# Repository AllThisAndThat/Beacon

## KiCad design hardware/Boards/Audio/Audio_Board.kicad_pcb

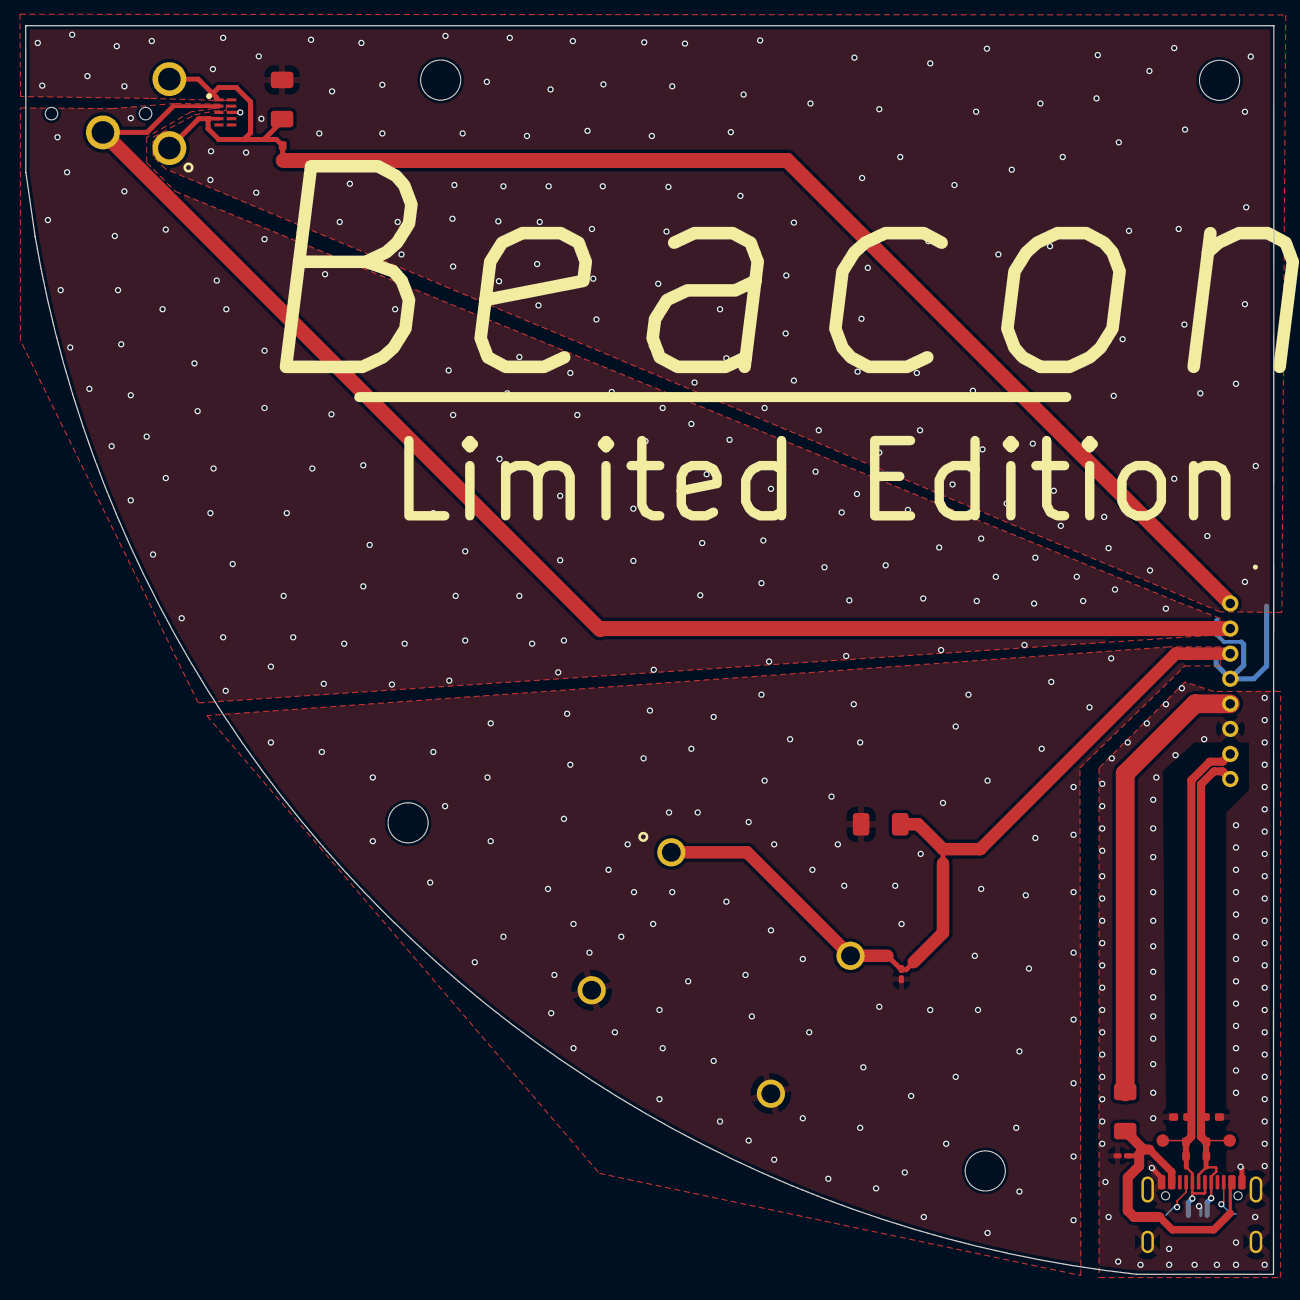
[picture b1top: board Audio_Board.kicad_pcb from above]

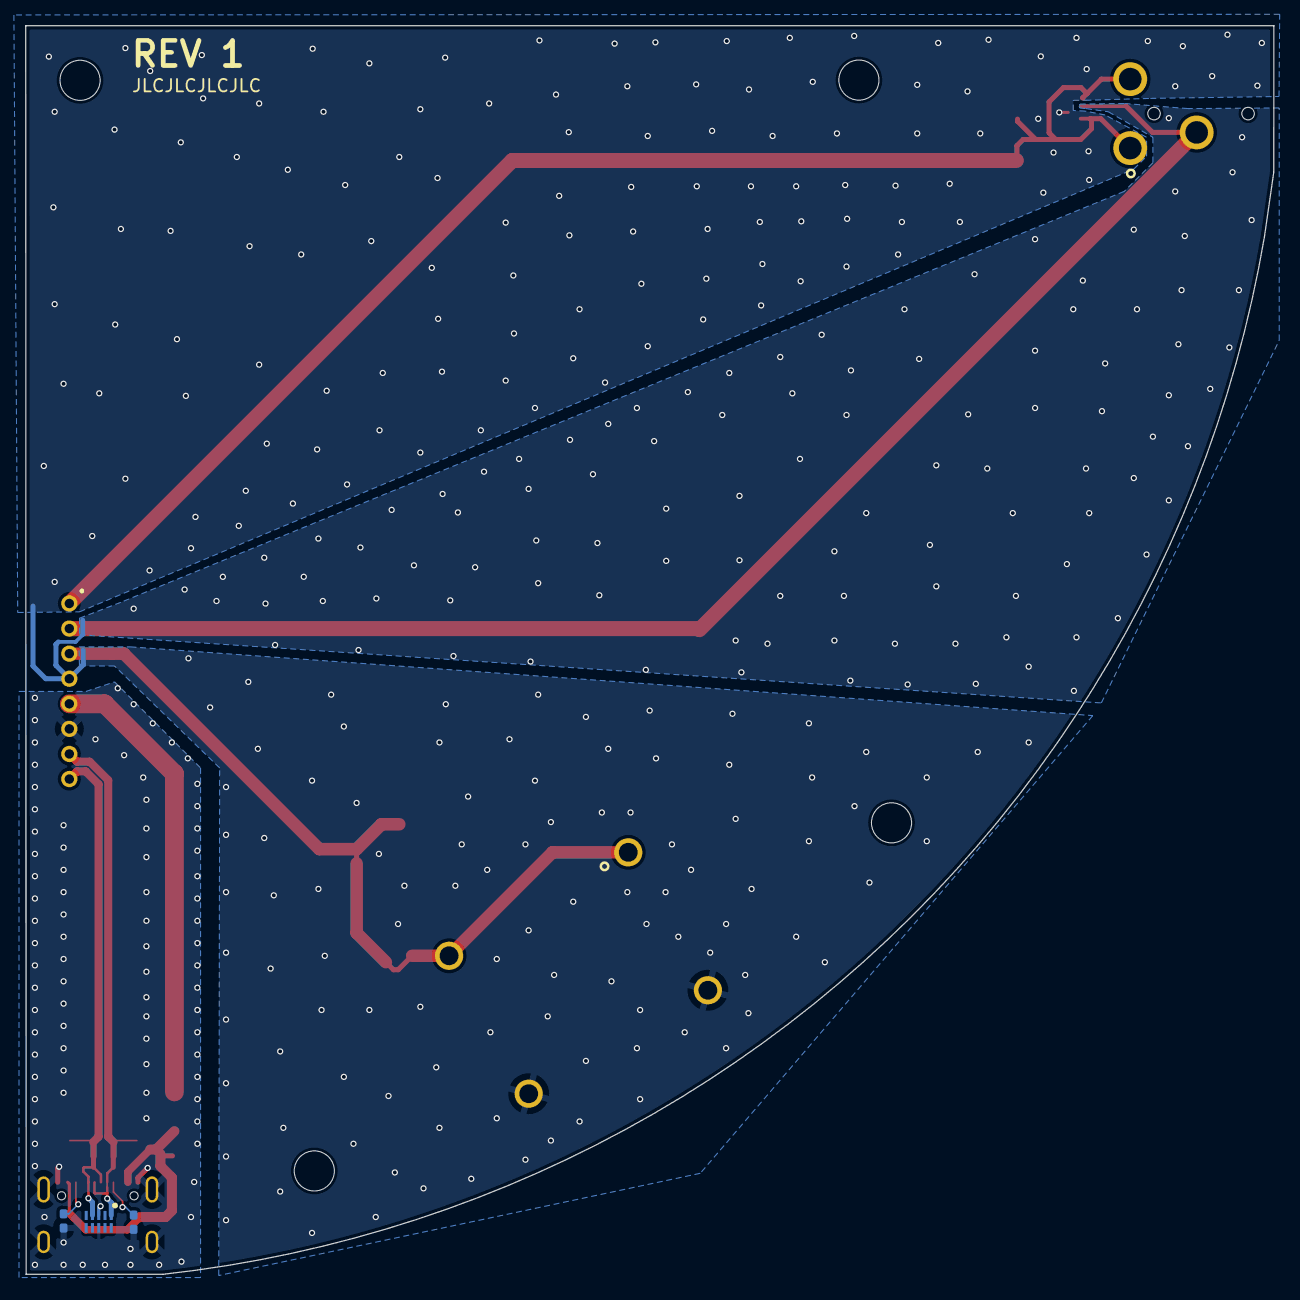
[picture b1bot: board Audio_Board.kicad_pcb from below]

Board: 6 copper layers, 99.5 x 99.6 mm, 22 parts (3 on the bottom side), 10 nets.

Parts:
Audio: Board
C509, C514: 1u00_1206_10_T; 1206_3216Metric_Handsolder
C531, C532: ????_0402_25; 0402_1005Metric_Handsolder
D502: ESDZV5HS-1BF4; 0201_0804Metric_Handsolder
D504, D505: PESD4USB5B; PESD4USB5BTBSX
D506: TVSL02V03C011; 0201_0804Metric_Handsolder
F502: 1A1_1206_08; 1206_3216Metric_Handsolder
J105: Conn_01x08_Pin; CONN_1x08_P2.00mm_Horizontal
J503, J505, J508, J511: 0402; 0402_CUT-N-JUMP
J509: Conn_01x03_Pin; STX3000
J510: USB_C_Receptacle_USB2.0; USB4105-GF-A
J513: Conn_01x02_Pin; NYS2162U
R517, R518: 5k10_0402_010; 0402_1005Metric_Handsolder
TP507: USB_DN; Testpoint_Pad_D1.0mm
TP508: USB_DP; Testpoint_Pad_D1.0mm

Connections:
Board_0-/Audio_Board/+5V: F502.2, J105.5
Board_0-/Audio_Board/AUDIO_GND_SEN: D504.2, J105.2, J509.2
Board_0-/Audio_Board/AUDIO_HP: C509.1, D504.1, D504.4, J105.1, J503.1, J503.2, J509.1, J509.3
Board_0-/Audio_Board/AUDIO_SP: C514.1, D506.1, J105.3, J505.1, J505.2, J513.1
Board_0-/Audio_Board/USB_DN: C531.2, D505.1, J105.7, J508.1, J508.2, J510.A7 (D-), J510.B7 (D-), TP507.1
Board_0-/Audio_Board/USB_DP: C532.2, D505.4, J105.8, J510.A6 (D+), J510.B6 (D+), J511.1, J511.2, TP508.1
Board_0-GND: C509.2, C514.2, C531.1, C532.1, D502.2, D504.3 (GND), D504.8 (GND), D505.3 (GND), D505.8 (GND), D506.2, J105.4, J105.6, J510.A1 (GND), J510.A12 (GND), J510.B1 (GND), J510.B12 (GND), J510.S1 (SHIELD), J513.2, R517.1, R518.1
Board_0-Net-(D502-Pad1): D502.1, F502.1, J510.A4 (VBUS), J510.A9 (VBUS), J510.B4 (VBUS), J510.B9 (VBUS)
Board_0-Net-(J510-CC1): J510.A5 (CC1), R517.2
Board_0-Net-(J510-CC2): J510.B5 (CC2), R518.2

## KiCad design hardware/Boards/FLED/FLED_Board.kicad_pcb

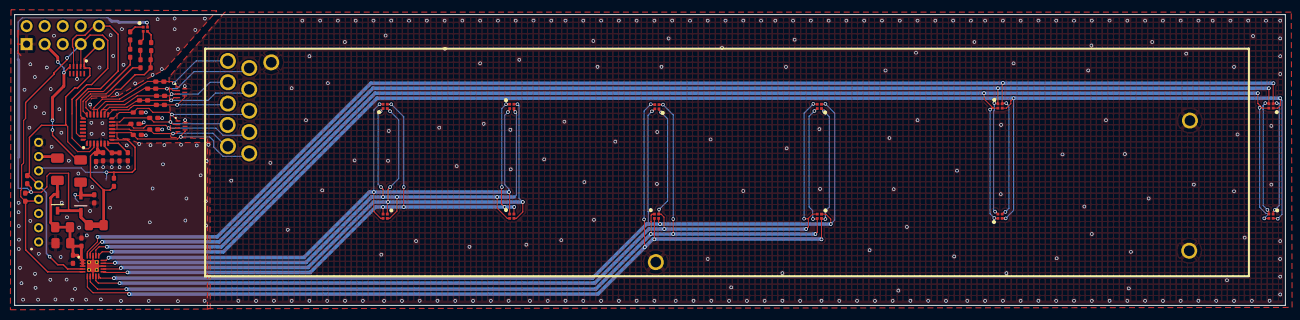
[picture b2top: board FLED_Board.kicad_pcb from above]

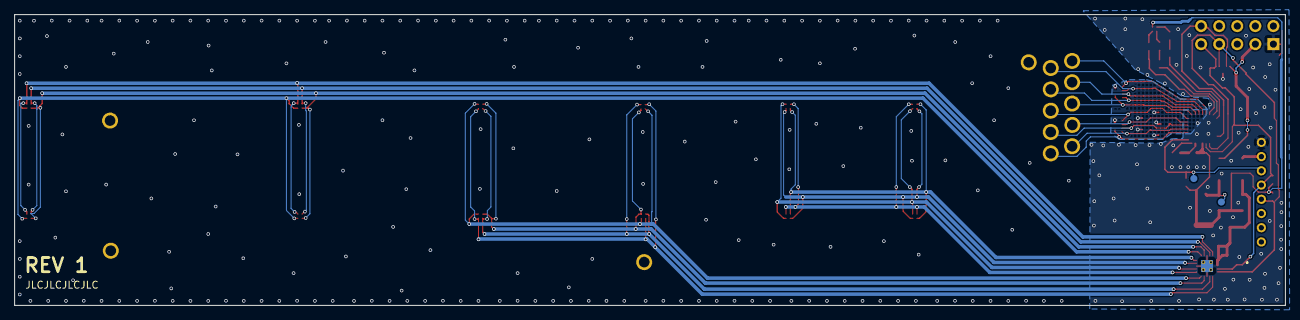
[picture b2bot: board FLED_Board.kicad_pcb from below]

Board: 6 copper layers, 178.7 x 40.9 mm, 71 parts (3 on the bottom side), 42 nets.

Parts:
C303, C403, C404, C408: 1u00_0402_10; 0402_1005Metric_Handsolder
C401, C407, C409: 100n_0402_16; 0402_1005Metric_Handsolder
C402: 10u0_0805_16; 0805_2012Metric_Handsolder
C405: 10n0_0402_25; 0402_1005Metric_Handsolder
C406, C410, C411, C412, C413: ????_0402_25; 0402_1005Metric_Handsolder
D401, D402, D403, D404, D405, D406, D407, D408, D409, D410, D411, D412, D417: UHD1110; UHD1110FKACL1A13r3q1BBQFMF3
D413, D414: 1N4148WX-TP; SOD2512X115N
D415: PESD4USB5B; PESD4USB5BTBSX
D416, D418: PUSB3TB6AZ
F401, F402: 1A1_1206_08; 1206_3216Metric_Handsolder
FLED: Board
H401, H402, H403, H404, H405, H411, H413, H415, H417, H423, H425, H426, H427, H428: Plated_Through_Hole; Plated_Hole_D1.5mm
J102: Conn_01x08_Pin; CONN_1x08_P2.00mm_Horizontal
J401, J408: 0805; 0805_CUT-N-JUMP
J402, J403, J405, J406, J407, J409: 0402; 0402_CUT-N-JUMP
J404: Conn_02x05_Odd_Even; PinHeader_2x05_P2.54
R401, R402: 4k70_0402_010; 0402_1005Metric_Handsolder
R403: 1k00_0402_010; 0402_1005Metric_Handsolder
R405, R407: 0330_0402_010; 0402_1005Metric_Handsolder
R406, R408: 0100_0402_010; 0402_1005Metric_Handsolder
R409: 47k0_0402_010; 0402_1005Metric_Handsolder
TP401: TOUCH_INT; Testpoint_Pad_D1.0mm
TP403: +3V3_DEBUG; Testpoint_Pad_D1.0mm
U401: KTD20XXEUAC-TR; UQFN-20-1EP_3x3mm_P0.4mm_EP1.7x1.7mm_ThermalVias
U402: IQS525BLQNR; QFN-28_4x4mm_P0.5mm

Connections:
Board_0-/Fret_Assembly/+3V3: C303.2, C401.2, C402.2, D413.2 (A), F401.2, J401.1, J401.2, U401.1 (VIN), U401.2 (VIN), U401.3 (VCC)
Board_0-/Fret_Assembly/+3V3_DEBUG: D415.5, F402.1, J404.3
Board_0-/Fret_Assembly/+3V3_EXT: F401.1, J102.7
Board_0-/Fret_Assembly/+3V3_PROTECT: C403.2, C405.2, D413.1 (K), D414.1 (K), D417.4, J408.1, J408.2, R401.2, R402.2, R409.1, U402.4 (VDDHI)
Board_0-/Fret_Assembly/BLED: R408.1, U402.22 (PD4)
Board_0-/Fret_Assembly/GLED: R406.1, U402.21 (PD3)
Board_0-/Fret_Assembly/I2C1_SCLK: D415.1, J102.5, J404.9, R401.1, U401.4 (SCL), U402.3 (SCL)
Board_0-/Fret_Assembly/I2C1_SDA: D415.2, J102.4, J404.7, R402.1, U401.5 (SDA), U402.2 (SDA)
Board_0-/Fret_Assembly/LEDA1: D401.3, D402.2, D403.1, D404.4, U401.6 (LEDA1)
Board_0-/Fret_Assembly/LEDA2: D401.2, D402.1, D403.4, D404.3, U401.7 (LEDA2)
Board_0-/Fret_Assembly/LEDA3: D401.1, D402.4, D403.3, D404.2, U401.9 (LEDA3)
Board_0-/Fret_Assembly/LEDA4: D401.4, D402.3, D403.2, D404.1, U401.10 (LEDA4)
Board_0-/Fret_Assembly/LEDB1: D405.3, D406.2, D407.1, D408.4, U401.11 (LEDB1)
Board_0-/Fret_Assembly/LEDB2: D405.2, D406.1, D407.4, D408.3, U401.12 (LEDB2)
Board_0-/Fret_Assembly/LEDB3: D405.1, D406.4, D407.3, D408.2, U401.14 (LEDB3)
Board_0-/Fret_Assembly/LEDB4: D405.4, D406.3, D407.2, D408.1, U401.15 (LEDB4)
Board_0-/Fret_Assembly/LEDC1: D409.3, D410.2, D411.1, D412.4, U401.16 (LEDC1)
Board_0-/Fret_Assembly/LEDC2: D409.2, D410.1, D411.4, D412.3, U401.17 (LEDC2)
Board_0-/Fret_Assembly/LEDC3: D409.1, D410.4, D411.3, D412.2, U401.19 (LEDC3)
Board_0-/Fret_Assembly/LEDC4: D409.4, D410.3, D411.2, D412.1, U401.20 (LEDC4)
Board_0-/Fret_Assembly/RLED: J409.1, J409.2, R403.1, U402.20 (PD2)
Board_0-/Fret_Assembly/RX0: C406.2, D418.5, H411.1, U402.10 (RX0/TX9)
Board_0-/Fret_Assembly/RX1: C410.2, D418.4, H413.1, U402.11 (RX1/TX8)
Board_0-/Fret_Assembly/RX2: C411.2, D418.3, H415.1, U402.12 (RX2/TX7)
Board_0-/Fret_Assembly/RX3: C412.2, D418.2, H417.1, U402.13 (RX3/TX6)
Board_0-/Fret_Assembly/RX4: C413.2, D418.1, H423.1, U402.14 (RX4/TX5)
Board_0-/Fret_Assembly/TOUCH_INT: J102.6, R409.2, TP401.1, U402.8 (RDY)
Board_0-/Fret_Assembly/TOUCH_PROGM: D415.4, J404.10, U402.27 (PGM)
Board_0-/Fret_Assembly/TX0: D416.1, H401.1, J402.1, J402.2, U402.19 (TX0)
Board_0-/Fret_Assembly/TX1: D416.2, H402.1, J403.1, J403.2, U402.18 (TX1)
Board_0-/Fret_Assembly/TX2: D416.3, H403.1, J405.1, J405.2, U402.17 (RX7/TX2)
Board_0-/Fret_Assembly/TX3: D416.4, H404.1, J406.1, J406.2, U402.16 (RX6/TX3)
Board_0-/Fret_Assembly/TX4: D416.5, H405.1, J407.1, J407.2, U402.15 (RX5/TX4)
Board_0-GND: C303.1, C401.1, C402.1, C403.1, C404.1, C405.1, C406.1, C407.1, C408.1, C409.1, C410.1, C411.1, C412.1, C413.1, D415.3 (GND), D415.8 (GND), D416.7 (GND), D418.7 (GND), H425.1, H426.1, H427.1, H428.1, J102.8, J404.1, U401.8 (GND), U401.13 (GND), U401.18 (GND), U401.EP (GND), U402.5 (VSS)
Board_0-Net-(D414-A): C404.2, D414.2 (A), F402.2, TP403.1
Board_0-Net-(D417-Pad1): D417.1, R407.2
Board_0-Net-(D417-Pad2): D417.2, R405.2
Board_0-Net-(D417-Pad3): D417.3, R403.2
Board_0-Net-(R405-Pad1): R405.1, R406.2
Board_0-Net-(R407-Pad1): R407.1, R408.2
Board_0-Net-(U402-NRST): C409.2, U402.7 (NRST)
Board_0-Net-(U402-VREG): C407.2, C408.2, U402.6 (VREG)

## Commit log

2024-10-27 Working on new pinManager concept
2024-12-01 Got Uart_printing working
2024-12-02 Got LED controller driver wrapper library working
2024-12-12 Added functionality to LedDriver
    * Setup test for LedDriver
    * Set heartbeat in main to freertos task
    * Added the following:
    * On and off functions
    * Bad duty rejection
    * Duty to resolution adjustment.
2024-12-15 Got Status_LED libary functioning
    Made small fixes to Led_Driver.
    Renamed/reorganized pin_assignment to reserved_objects.
    Created and got status_led working.
    Started a timer.h wrapper.
2024-12-23 Worked on Spi and I2C classes
2024-12-28 Wrote LTR_303ALS driver
2024-12-28 KTS1622 Driver started
    * Wrote test for ambient light sensor
    * Started kts1622 driver
2024-12-29 Started I2S and Max9867 drivers
    * Made test for kts1622
    * Created driver for i2s
    * Created driver for max9867
    * Polished kts1622 - removed interrrupts on esp side and added debounce fuctionality
2025-01-05 Progress on max9867
    * Headphone output detect working
    * Started I2S communication between ICs
2025-01-16 Got CODEC Echo working
2025-01-20 Significant progress on Max9867
    * added DAC I2C commands
    * added ADC I2C commands
    * added task for audio processing
2025-01-27 Started work on IMU
    * Developed SPI and BMI323 drivers
    * Renamed and reordered reserve library
2025-02-02 Significant progress on BMI323
    * Read, write, and multiread registers working.
    * BMI323 configuration working
    * Reading acc and gyro data successfully
2025-02-06 Started IS31FL3741 driver
    * Class setup
    * Initiate
    * Unlock
    * Some configuration registers
2025-02-09 Implemented several IS31fl3741 methods
    * Reset all leds
    * Set specific led by num
    * set specific led by row, column, color
2025-02-13 Improvements to IS31FL3741 driver
    * Created set_rgb_led method with improved clarity
    * Fixed reset fails first time bug
    * Fixed ghosting bug
2025-03-03 Started CAP1188 driver
2025-04-14 Starting Beacon Lite Version
    * Achieved Old hardware files for reference.
    * Started new Kicad Design
2025-04-20 Started ST project. Create sch symbols.
2025-04-23 Minor schematic and symbol updates
2025-05-09 Started programming NUCLEO-H533 in VSCODE
    * Able to use C++ and C
    * Successful able to debug
    * Can blink an LED when button is pressed via an interrupt.
2025-05-11 Converted the project main into C++ only. Got timer driver functioning
    * Started new beacon_lite library.
    * Modified CMakeLists.txt to get new library working.
    * Removed main.c so it can function with main.cpp file only.
    * Basic structure of timer driver.
2025-05-12 Three PWM working
    Timer can spawn three different PWM for the debug RGB.
    Created a beacon library cmake file.
    Will throw an error if main.c and main.cpp both exist.
2025-05-14 Implemented i2c_master driver
    Can read and write with I2C class.
    Swapped to main.c calling cpp_main.cpp so code regenerate is in sync.
    Changed timer naming to debug_led and added color feature
2025-05-14 Started ltr_303als library
    Got basic polling of ltr_303als working.
    All hardware is initialized in main.c. Removed initializers from I2C_master and debug_led
2025-05-18 Got interrupt software working for LTR-303als driver.
    * Added to LTR-303als class
    * Setup automatic interrupts for when ambient light changes by a certain percentage.
2025-05-18 Freertos tasks working
    Setup two tasks
    * Basic heartbeat task
    * ltr_303als brightness tasks
    Setup freertos flag to only enter tasks on interrupt
    Moved ltr_303als software out of cpp_main.cpp
2025-05-18 Got DMA transferring to timer for led strip with correct frequency and duties
2025-05-20 Got led strip working
    * Currently uses a large array for each pixel.
2025-05-20 Made neopixel_4310 library with HSL values
2025-05-21 Copied over IS31FL3741 library and got it working
    * integrated I2C address and ports into syscfg for easier development
2025-05-22 Minor reformatting of the IS31fl3741 library
2025-05-23 Got DMA to transfer led colors to I2C peripheral for is31fl3741 library
2025-05-25 Updated is31fl3741
    * uses dma transfers to refresh screen
    * setupt is31fl3741 rtos task
    * converted all rtos tasks to static allocation
    * added a few methods to is31fl3741 such as set_pixel, set_row, set_col, set_all_pixels, set_all_pixels_blank
2025-05-26 Single ADC channel working in main.c
    * ADC streaming data to buffer over dma.
    * dma then streams data over UART for SerialPlot software
    * Setup single analog watchdog
2025-05-28 Prototyped press detection. Added Q library to start pitch detection.
    * Able to accurately detect presses for small test size of 2 strings and 2 frets.
    * Had to insulate strings from each other on bridge.
    * Annoying clicking from modulated strings. Hope to improve by doing the following: AC couple strings, lower to 1.8V, filtering
    * Set ADC to oversample.
    * Added Q library for pitch detection
2025-05-29 Working single pickup active string amplitude sensing - basic algorithm in main.c
2025-05-31 Reformatted drivers. Added I2C_device functionality. Added Ano Rotary Library
    * Ano rotary able to poll encoder and all 5 buttons.
    * Modified I2C library to i2c_device which wraps hal_i2c functions. Stores device address, i2c bus, and 8/16 bit register mode
2025-06-01 Added task for Ano_Rotary to read on interrupt
    * Moved some interrupts to main.cpp. Might created shared interrupt folder later.
    * Able to run IS31fl3741, ltr_303, heartbeat, and ano_rotary task all working simultaneously.
    * Open bug in new i2c_device verify write function
    * I2C bus failures fixed with stronger pullup resistors
2025-06-04 Format fixing, bootup failures fixed.
    Added acknowlegement checking to I2c_device.
    When device initiates i2c_device handles, wait until acknowledgment.
    Added function so users of the i2c_device class can wait for the device to be ready when doing things like software resetting.
    Modifying and unifing formatting for all Beacon drivers.
    Currently have an issue with slow is31fl3741 boot.
2025-06-05 Fixed I2C DMA and worked on IS31fl3741
    Added dmaWrite to I2cDevice library and used interrupt to have function wait until transfer complete.
    Changed is31fl3741 refreshBrightness function to use DMA.
2025-06-07 Remodeling is31fl3741 driver to match standard formatting.
2025-06-07 Continue cleaning and reformatting is31fl3741 library.
    * Created math library to commonly shared math function used throughout this project.
    * Setup compile time settings for IS31FL3741 so you can easily adjust driver for different hardware.
    * Syscfg has hardware directive to choose between different hardware setups.
    * Moved is31Fl3741 inside a namespace to help prevent global clutter.
2025-06-08 Updated neopixel_4310 with new formatting
    * Made neopixel more dynamic depending on timer used and the period of the timer.
2025-06-15 Began Beacon Tower Schematic
2025-06-17 Started assigning footprints. Tweaking schematic.
